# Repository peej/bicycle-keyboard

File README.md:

Bicycle is a 58 key ortholinear split keyboard PCB with a 5 key thumb cluster.

A more ergonomic version of the Let's Split keyboard, it adds an additional row to the matrix for use by a 30 degree angled thumb cluster of keys. Designed to be easy to build, it only supports serial communication over a TRRS cable and no LED support. The PCB is reversible, meaning that you need two of the same PCB to create a full keyboard.

Documentation is a work in progress.

# BOM

* 2 PCBs, Gerber files for printing can be found in the repo.
* 58 MX compatible switches.
* 58 1n4148 diodes.
* 2 Pro Micros.
* 2 PJ320A 3.5mm TRRS jacks.
* TRRS cable and micro USB cable.

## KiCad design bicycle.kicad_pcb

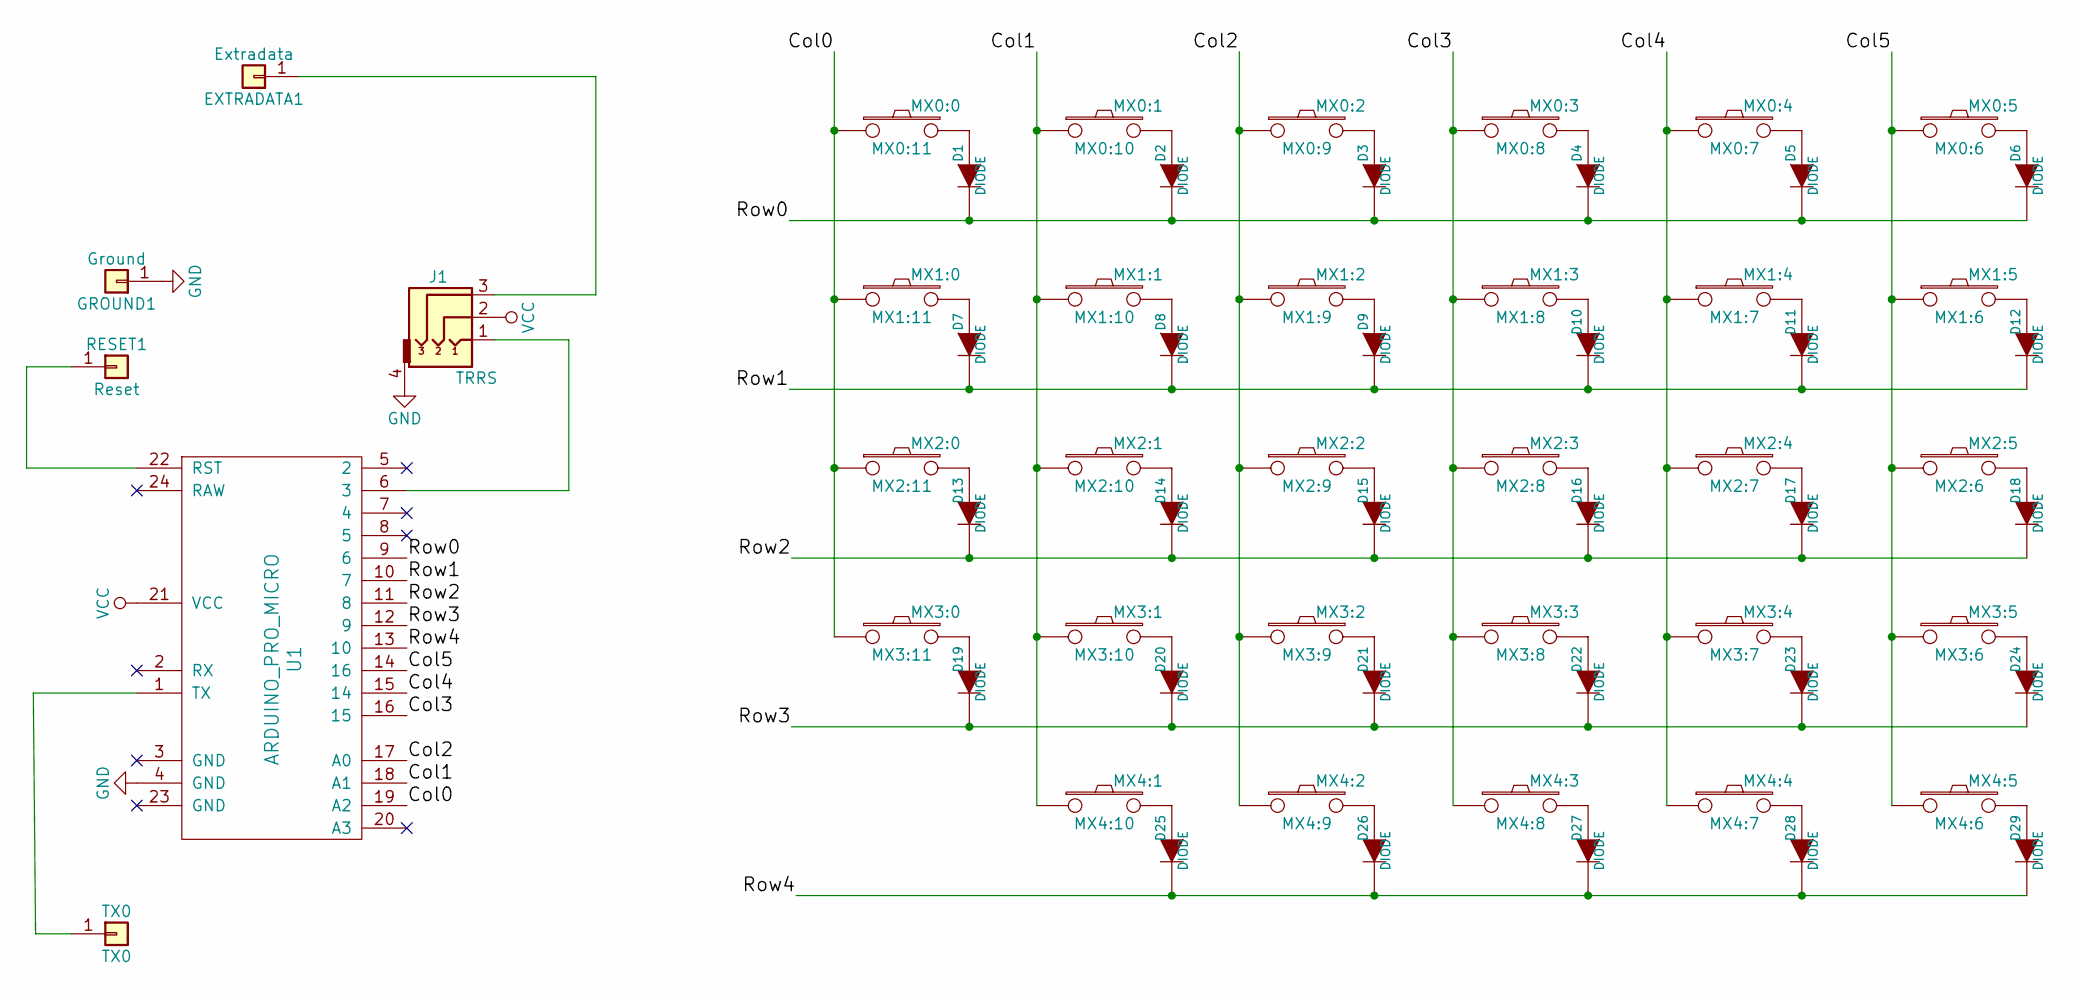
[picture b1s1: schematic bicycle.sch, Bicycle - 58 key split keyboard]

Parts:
D1, D2, D3, D4, D5, D6, D7, D8, D9, D10, D11, D12, D13, D14, D15, D16, D17, D18, D19, D20, D21, D22, D23, D24, D25, D26, D27, D28, D29: DIODE; D_SOD123_axial
EXTRADATA1: Extradata; PIN_1_SQUARE
GROUND1: Ground; PIN_1_SQUARE
J1: TRRS; PJ320A_3.5mm_Jack
MX0:0: MX0:11; MX_DoubleSided
MX0:1: MX0:10; MX_DoubleSided
MX0:2: MX0:9; MX_DoubleSided
MX0:3: MX0:8; MX_DoubleSided
MX0:4: MX0:7; MX_DoubleSided
MX0:5: MX0:6; MX_DoubleSided
MX1:0: MX1:11; MX_DoubleSided
MX1:1: MX1:10; MX_DoubleSided
MX1:2: MX1:9; MX_DoubleSided
MX1:3: MX1:8; MX_DoubleSided
MX1:4: MX1:7; MX_DoubleSided
MX1:5: MX1:6; MX_DoubleSided
MX2:0: MX2:11; MX_DoubleSided
MX2:1: MX2:10; MX_DoubleSided
MX2:2: MX2:9; MX_DoubleSided
MX2:3: MX2:8; MX_DoubleSided
MX2:4: MX2:7; MX_DoubleSided
MX2:5: MX2:6; MX_DoubleSided
MX3:0: MX3:11; MX_DoubleSided
MX3:1: MX3:10; MX_DoubleSided
MX3:2: MX3:9; MX_DoubleSided
MX3:3: MX3:8; MX_DoubleSided
MX3:4: MX3:7; MX_DoubleSided
MX3:5: MX3:6; MX_DoubleSided
MX4:1: MX4:10; MX_DoubleSided
MX4:2: MX4:9; MX_DoubleSided
MX4:3: MX4:8; MX_DoubleSided
MX4:4: MX4:7; MX_DoubleSided
MX4:5: MX4:6; MX_DoubleSided
RESET1: Reset; PIN_1_SQUARE
TX0: TX0; PIN_1_SQUARE
U1: ARDUINO_PRO_MICRO

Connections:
/Col0: MX0:0.1, MX1:0.1, MX2:0.1, MX3:0.1, U1.19 (A2)
/Col1: MX0:1.1, MX1:1.1, MX2:1.1, MX3:1.1, MX4:1.1, U1.18 (A1)
/Col2: MX0:2.1, MX1:2.1, MX2:2.1, MX3:2.1, MX4:2.1, U1.17 (A0)
/Col3: MX0:3.1, MX1:3.1, MX2:3.1, MX3:3.1, MX4:3.1, U1.16 (15)
/Col4: MX0:4.1, MX1:4.1, MX2:4.1, MX3:4.1, MX4:4.1, U1.15 (14)
/Col5: MX0:5.1, MX1:5.1, MX2:5.1, MX3:5.1, MX4:5.1, U1.14 (16)
/Row0: D1.2 (K), D2.2 (K), D3.2 (K), D4.2 (K), D5.2 (K), D6.2 (K), U1.9 (6)
/Row1: D7.2 (K), D8.2 (K), D9.2 (K), D10.2 (K), D11.2 (K), D12.2 (K), U1.10 (7)
/Row2: D13.2 (K), D14.2 (K), D15.2 (K), D16.2 (K), D17.2 (K), D18.2 (K), U1.11 (8)
/Row3: D19.2 (K), D20.2 (K), D21.2 (K), D22.2 (K), D23.2 (K), D24.2 (K), U1.12 (9)
/Row4: D25.2 (K), D26.2 (K), D27.2 (K), D28.2 (K), D29.2 (K), U1.13 (10)
GND: GROUND1.1, J1.4, U1.4 (GND)
unnamed: D1.1 (A), MX0:0.2
unnamed: D2.1 (A), MX0:1.2
unnamed: D3.1 (A), MX0:2.2
unnamed: D4.1 (A), MX0:3.2
unnamed: D5.1 (A), MX0:4.2
unnamed: D6.1 (A), MX0:5.2
unnamed: D7.1 (A), MX1:0.2
unnamed: D8.1 (A), MX1:1.2
unnamed: D9.1 (A), MX1:2.2
unnamed: D10.1 (A), MX1:3.2
unnamed: D11.1 (A), MX1:4.2
unnamed: D12.1 (A), MX1:5.2
unnamed: D13.1 (A), MX2:0.2
unnamed: D14.1 (A), MX2:1.2
unnamed: D15.1 (A), MX2:2.2
unnamed: D16.1 (A), MX2:3.2
unnamed: D17.1 (A), MX2:4.2
unnamed: D18.1 (A), MX2:5.2
unnamed: D19.1 (A), MX3:0.2
unnamed: D20.1 (A), MX3:1.2
unnamed: D21.1 (A), MX3:2.2
unnamed: D22.1 (A), MX3:3.2
unnamed: D23.1 (A), MX3:4.2
unnamed: D24.1 (A), MX3:5.2
unnamed: D25.1 (A), MX4:1.2
unnamed: D26.1 (A), MX4:2.2
unnamed: D27.1 (A), MX4:3.2
unnamed: D28.1 (A), MX4:4.2
unnamed: D29.1 (A), MX4:5.2
unnamed: EXTRADATA1.1, J1.3
unnamed: J1.1, U1.6 (3)
unnamed: RESET1.1, U1.22 (RST)
unnamed: TX0.1, U1.1 (TX)
VCC: J1.2, U1.21 (VCC)

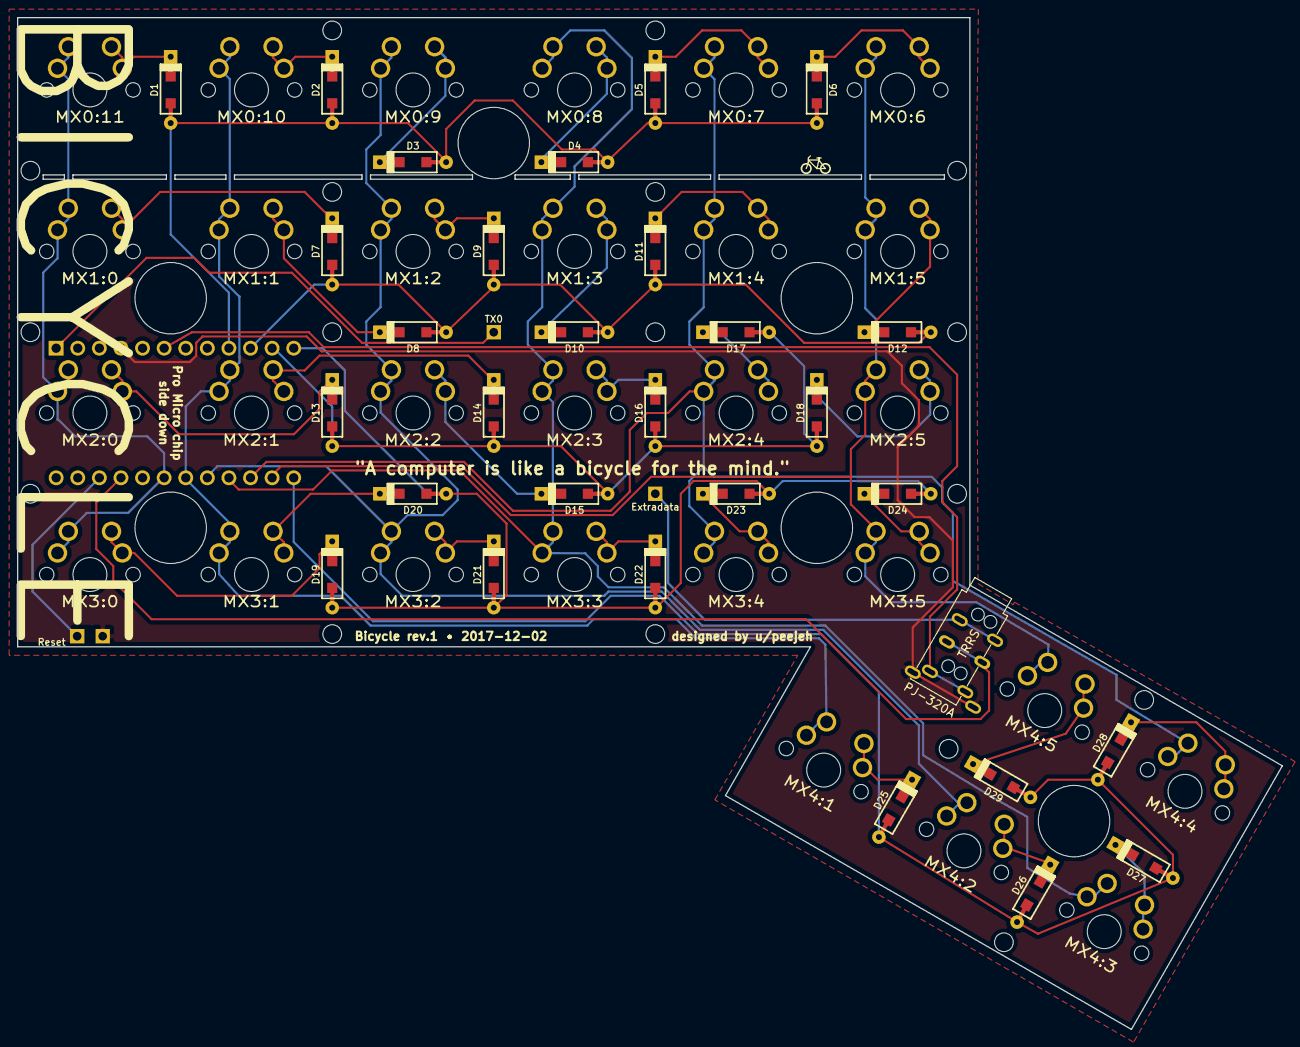
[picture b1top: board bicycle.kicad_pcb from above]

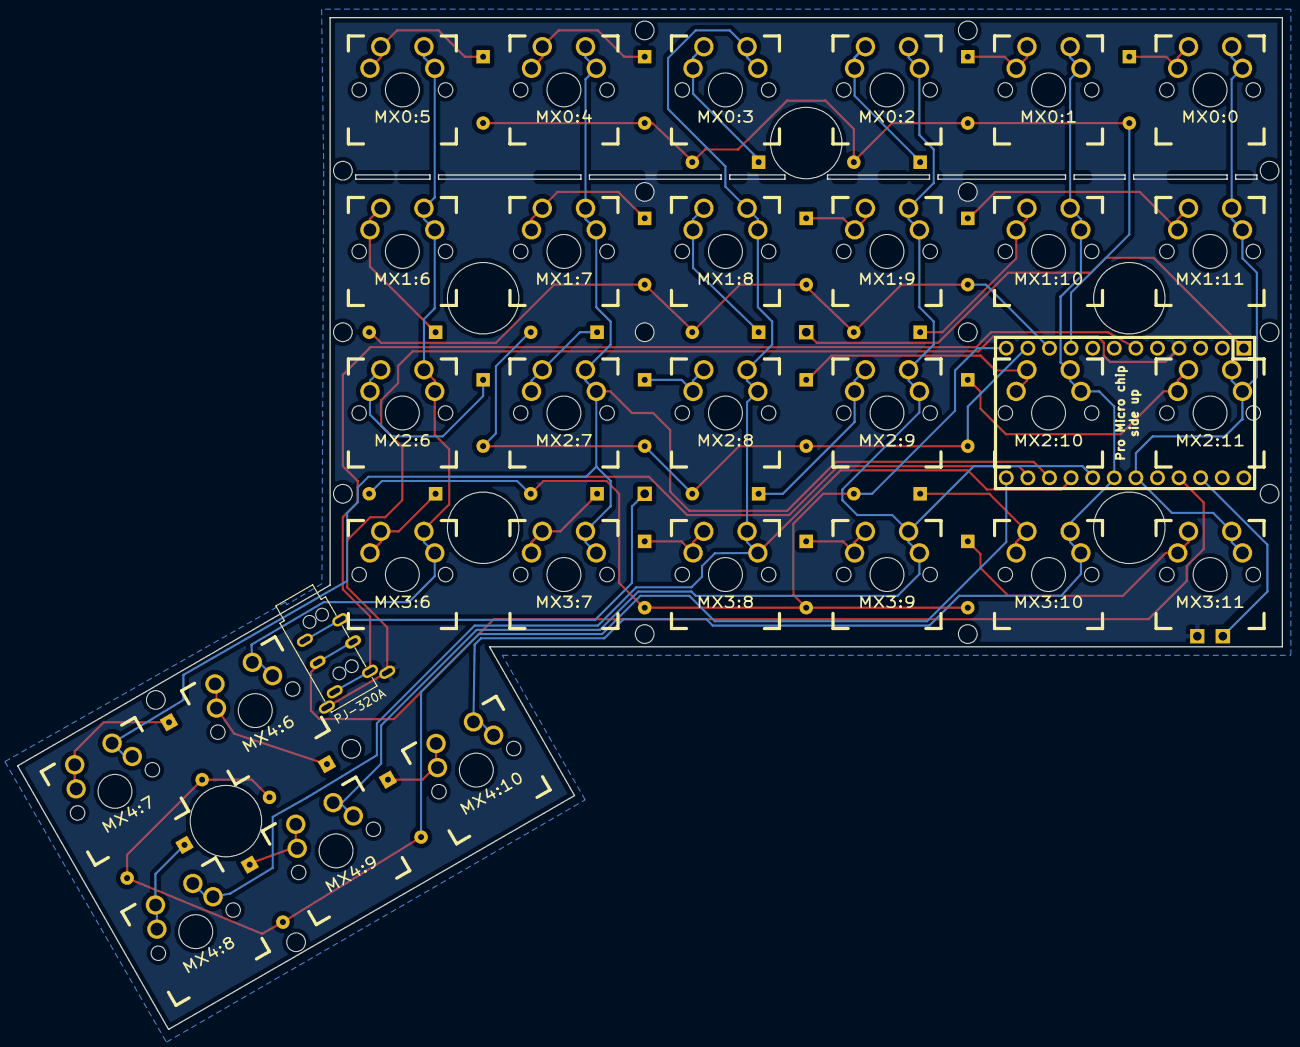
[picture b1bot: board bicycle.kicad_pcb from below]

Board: 2 copper layers, 148.8 x 119.0 mm, 87 parts (30 on the bottom side), 46 nets.

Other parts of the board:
M2, M2#2, M2#3, M2#4, M2#5, M2#6, M2#7, M2#8, M2#9, M2#10, M2#11, M2#12, M2#13, M2#14, M2#15, M2#16, M2#17: MountingHole_2.2mm_M2
M8, M8#2, M8#3, M8#4, M8#5, M8#6: MountingHole_8.4mm_M8

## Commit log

2017-12-06 Add plate PCB
2017-12-06 Add PCB files
2017-12-06 Add gerber files
2017-12-06 Add readme file
